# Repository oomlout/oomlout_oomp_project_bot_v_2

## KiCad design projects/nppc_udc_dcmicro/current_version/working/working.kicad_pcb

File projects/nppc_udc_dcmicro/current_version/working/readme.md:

# udc
 
## summary 
* id: nppc_udc_dcmicro
* user: nppc
* name: udc
* board: dcmicro
* repo: https://github.com/nppc/uDC
* src_file_repo_kicad_pcb: DCMicro.kicad_pcb
* src_file_repo_kicad_pcb_link: https://github.com/nppc/uDC/tree/master/DCMicro.kicad_pcb

* src_file_repo_sch: DCMicro.sch
* src_file_repo_sch_link: https://github.com/nppc/uDC/tree/master/DCMicro.sch
* full details link: https://github.com/oomlout/oomlout_oomp_project_bot_v_2/tree/main/projects/nppc_udc_dcmicro/current_version/working

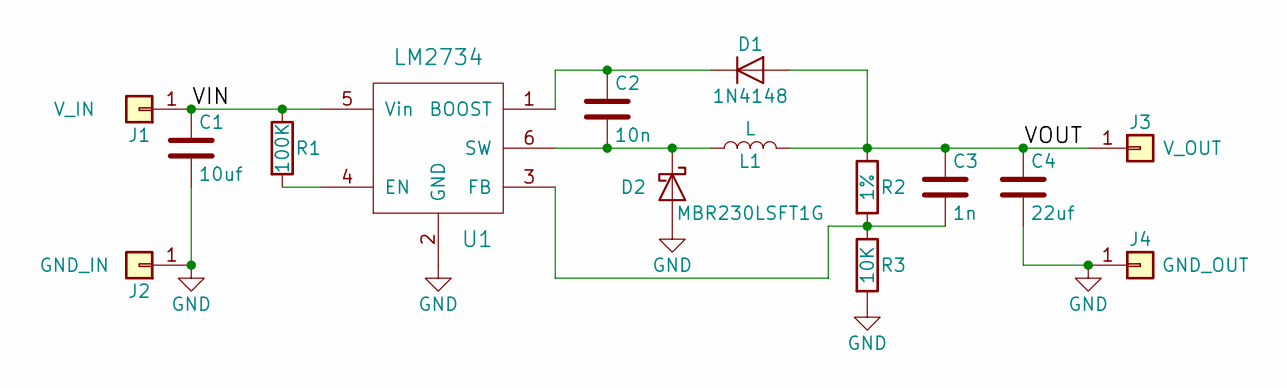
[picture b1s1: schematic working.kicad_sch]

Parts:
C1: 10uf; C_0603
C2: 10n; C_0402_NoSilk
C3: 1n; C_0402_NoSilk
C4: 22uf; C_0603
D1: 1N4148; D_SOD-523
D2: MBR230LSFT1G; D_SOD-123F
J1: V_IN; ESC_PWR_PAD
J2: GND_IN; ESC_PWR_PAD
J3: V_OUT; ESC_PWR_PAD
J4: GND_OUT; ESC_PWR_PAD
L1: L; Inductor-LPS4012
R1: 100K; R_0402_NoSilk
R2: 1%; R_0402_NoSilk
R3: 10K; R_0402_NoSilk
U1: LM2734; SOT-23-6

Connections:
/VIN: C1.1, J1.1, R1.1, U1.5 (Vin)
/VOUT: C3.1, C4.1, D1.2 (A), J3.1, L1.2, R2.1
GND: C1.2, C4.2, D2.2 (A), J2.1, J4.1, R3.2, U1.2 (GND)
unnamed: C2.1, D1.1 (K), U1.1 (BOOST)
unnamed: C2.2, D2.1 (K), L1.1, U1.6 (SW)
unnamed: C3.2, R2.2, R3.1, U1.3 (FB)
unnamed: R1.2, U1.4 (EN)

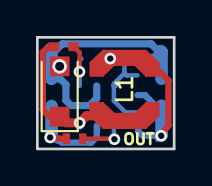
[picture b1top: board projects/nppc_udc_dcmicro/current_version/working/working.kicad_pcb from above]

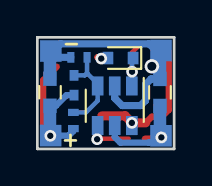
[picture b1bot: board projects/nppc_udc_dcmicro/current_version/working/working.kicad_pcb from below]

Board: 2 copper layers, 7.6 x 6.2 mm, 15 parts (11 on the bottom side), 7 nets.

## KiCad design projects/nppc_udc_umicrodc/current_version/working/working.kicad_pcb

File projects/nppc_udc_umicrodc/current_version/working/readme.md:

# udc
 
## summary 
* id: nppc_udc_umicrodc
* user: nppc
* name: udc
* board: umicrodc
* repo: https://github.com/nppc/uDC
* src_file_repo_kicad_pcb: uMicroDC/uMicroDC.kicad_pcb
* src_file_repo_kicad_pcb_link: https://github.com/nppc/uDC/tree/master/uMicroDC/uMicroDC.kicad_pcb

* src_file_repo_sch: uMicroDC/uMicroDC.sch
* src_file_repo_sch_link: https://github.com/nppc/uDC/tree/master/uMicroDC/uMicroDC.sch
* full details link: https://github.com/oomlout/oomlout_oomp_project_bot_v_2/tree/main/projects/nppc_udc_umicrodc/current_version/working

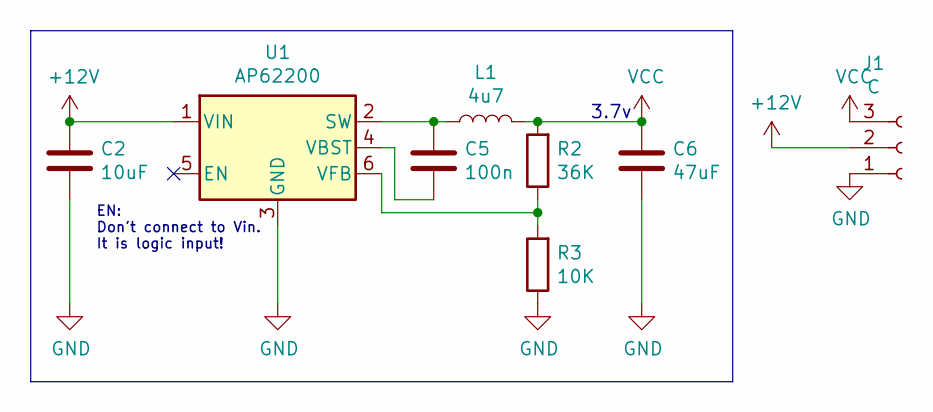
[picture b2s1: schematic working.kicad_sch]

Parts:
C2: 10uF; C_0805
C5: 100n; C_0603
C6: 47uF; C_0805
J1: C; Pin_Header_Angled_1x03_Pitch2.54mm
L1: 4u7; XFL2006-inductor
R2: 36K; R_0603
R3: 10K; R_0603
U1: AP62200; SOT-563

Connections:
+12V: C2.1, J1.2, U1.1 (VIN)
GND: C2.2, C6.2, J1.1, R3.1, U1.3 (GND)
unnamed: C5.1, L1.1, U1.2 (SW)
unnamed: C5.2, U1.4 (VBST)
unnamed: R2.1, R3.2, U1.6 (VFB)
VCC: C6.1, J1.3, L1.2, R2.2

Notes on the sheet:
3.7v
EN: Don't connect to Vin. It is logic input!

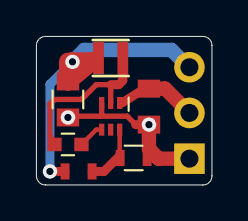
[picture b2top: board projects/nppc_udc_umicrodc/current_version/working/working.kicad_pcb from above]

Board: 2 copper layers, 9.8 x 8.2 mm, 8 parts (1 on the bottom side), 6 nets.

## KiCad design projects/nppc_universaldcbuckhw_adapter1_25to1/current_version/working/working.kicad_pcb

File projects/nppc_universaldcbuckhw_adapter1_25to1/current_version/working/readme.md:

# universaldcbuckhw
 
## summary 
* id: nppc_universaldcbuckhw_adapter1_25to1
* user: nppc
* name: universaldcbuckhw
* board: adapter1_25to1
* repo: https://github.com/nppc/UniversalDCBuckHW
* src_file_repo_kicad_pcb: KiCad/Adapter1-25to1/Adapter1-25to1.kicad_pcb
* src_file_repo_kicad_pcb_link: https://github.com/nppc/UniversalDCBuckHW/tree/master/KiCad/Adapter1-25to1/Adapter1-25to1.kicad_pcb

* src_file_repo_sch: KiCad/Adapter1-25to1/Adapter1-25to1.sch
* src_file_repo_sch_link: https://github.com/nppc/UniversalDCBuckHW/tree/master/KiCad/Adapter1-25to1/Adapter1-25to1.sch
* full details link: https://github.com/oomlout/oomlout_oomp_project_bot_v_2/tree/main/projects/nppc_universaldcbuckhw_adapter1_25to1/current_version/working

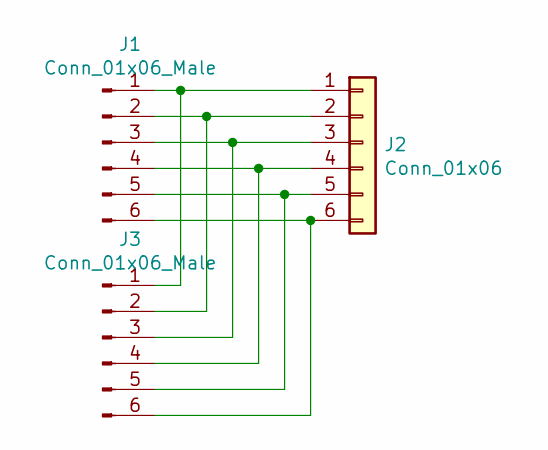
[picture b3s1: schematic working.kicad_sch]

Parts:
J1: Conn_01x06_Male; Pads_prog_6pin1.25mm
J2: Conn_01x06; JST_SH_6x1mm
J3: Conn_01x06_Male; Pin_Header_Angled_1x06_Pitch1.27mm

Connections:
unnamed: J1.1, J2.1, J3.1
unnamed: J1.2, J2.2, J3.2
unnamed: J1.3, J2.3, J3.3
unnamed: J1.4, J2.4, J3.4
unnamed: J1.5, J2.5, J3.5
unnamed: J1.6, J2.6, J3.6

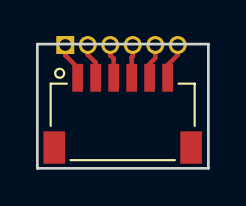
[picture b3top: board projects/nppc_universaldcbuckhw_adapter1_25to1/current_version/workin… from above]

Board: 2 copper layers, 9.5 x 6.9 mm, 3 parts (1 on the bottom side), 6 nets.

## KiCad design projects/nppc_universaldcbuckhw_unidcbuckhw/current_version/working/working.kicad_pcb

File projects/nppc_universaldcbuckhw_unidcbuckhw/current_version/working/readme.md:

# universaldcbuckhw
 
## summary 
* id: nppc_universaldcbuckhw_unidcbuckhw
* user: nppc
* name: universaldcbuckhw
* board: unidcbuckhw
* repo: https://github.com/nppc/UniversalDCBuckHW
* src_file_repo_kicad_pcb: KiCad/UniDCBuckHW.kicad_pcb
* src_file_repo_kicad_pcb_link: https://github.com/nppc/UniversalDCBuckHW/tree/master/KiCad/UniDCBuckHW.kicad_pcb

* src_file_repo_sch: KiCad/UniDCBuckHW.sch
* src_file_repo_sch_link: https://github.com/nppc/UniversalDCBuckHW/tree/master/KiCad/UniDCBuckHW.sch
* full details link: https://github.com/oomlout/oomlout_oomp_project_bot_v_2/tree/main/projects/nppc_universaldcbuckhw_unidcbuckhw/current_version/working

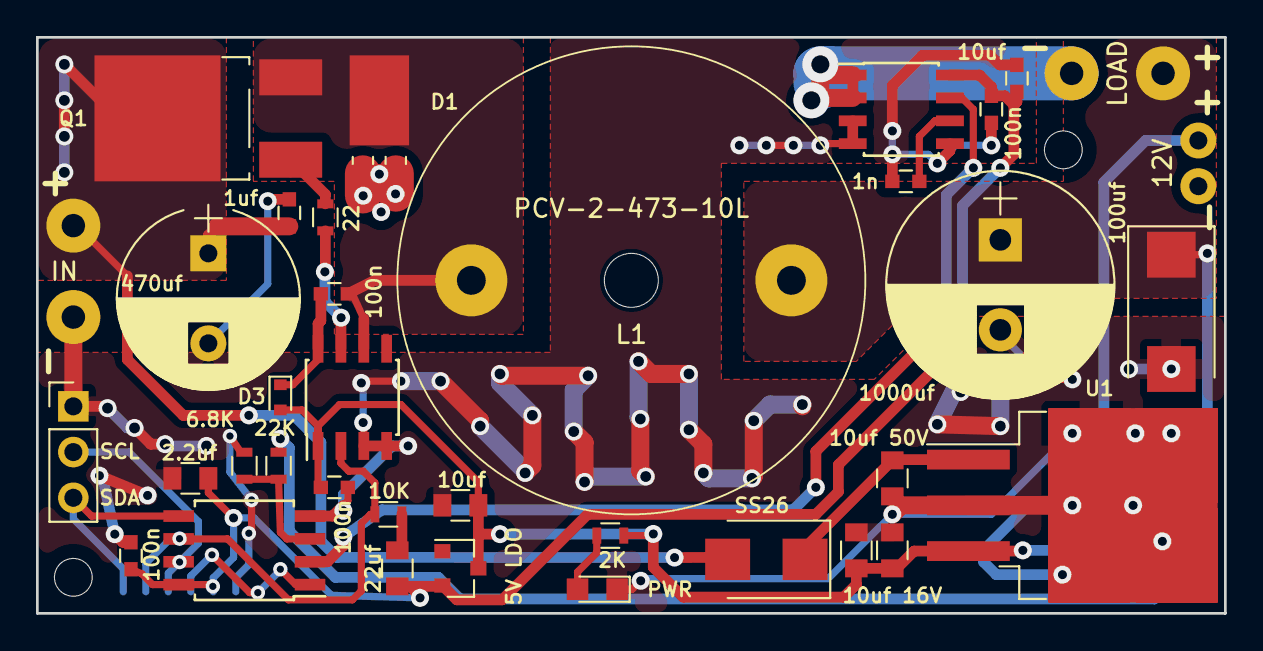
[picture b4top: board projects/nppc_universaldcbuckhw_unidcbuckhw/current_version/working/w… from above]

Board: 2 copper layers, 66.0 x 32.0 mm, 37 parts (1 on the bottom side), 19 nets.

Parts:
C1: 10uf 50V; C_0805
C2: 10uf; C_0805
C3, C5: 10uf 16V; C_0805
C4: 2.2uf; C_0805
C6: 470uf; CP_Radial_D10.0mm_P5.00mm
C7, C8, C11, C14: 100n; C_0603
C9: 1uf; C_0603
C10: 1000uf; CP_Radial_D12.5mm_P5.00mm
C12: 100uf; CP_Tantalum_Case-V_EIA-7343-20_Reflow
C13: 22uf; C_0805
C15: 1n; C_0603
C16: 10uf; C_0603
D1: PPS1045; D_Powermite3
D2: SS26; D_SMB
D3: 1N5819; D_SOD-523
D4: LED; LED_0805
J1: IN; Conn_Power
J2: 12V; Conn2pin_2.54mm
J3: i2c; Pin_Header_Straight_1x03_Pitch2.54mm
J4: LOAD; Conn_Power
J5: PROG; Pads_prog_6pin1.25mm
L1: 47uH; PCV-2-473-10L
Q1: IRLR8726PBF; TO-252-2_Rectifier
R1: 22K; R_0603
R2: 6.8K; R_0603
R3: 10K; R_0603
R4: 22; R_0603
R5: 2K; R_0603
U1: LM2940-12V; TO-263-3_TabPin2
U2: MCP1703-5V; SOT-23
U3: IR2101; SOIC-8_3.9x4.9mm_Pitch1.27mm
U4: ATTINY85-20SU; SOIJ-8_5.3x5.3mm_Pitch1.27mm
U5: ACS712-5; SOIC-8_3.9x4.9mm_Pitch1.27mm

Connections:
+5V: C4.2, C11.2, C13.2, C14.2, C16.2, J5.5, U2.2, U4.8, U5.8
+12V: C2.2, C3.2, C5.2, C7.2, D3.2, J2.2, R5.2, U1.3, U2.3, U3.1
/Isense: U4.2, U5.7
/PWM: J5.2, R3.2, U3.2, U4.6
/RST: J5.4, U4.1
/SCL: J3.2, J5.3, U4.7
/SDA: J3.3, J5.1, U4.5
/VOUT: C10.1, C12.1, J4.1, L1.2, R1.2
/Vsense: R1.1, R2.2, U4.3
GND: C1.1, C2.1, C3.1, C4.1, C5.1, C6.2, C7.1, C9.1, C10.2, C11.1, C12.2, C13.1, C14.1, C15.1, C16.1, D1.2, D4.1, J1.1, J2.1, J3.1, J5.6, R2.1, R3.1, U1.2, U2.1, U3.3, U3.4, U4.4, U5.3, U5.4, U5.5
unnamed: C1.2, D2.1, U1.1
unnamed: C6.1, C9.2, D2.2, J1.2, Q1.2
unnamed: C8.1, D1.1, L1.1, Q1.3, U3.6
unnamed: C8.2, D3.1, U3.8
unnamed: C15.2, U5.6
unnamed: D4.2, R5.1
unnamed: J4.2, U5.1, U5.2
unnamed: Q1.1, R4.1
unnamed: R4.2, U3.7

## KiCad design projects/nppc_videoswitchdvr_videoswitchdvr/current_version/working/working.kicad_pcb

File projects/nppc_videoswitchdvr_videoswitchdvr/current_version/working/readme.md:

# videoswitchdvr
 
## summary 
* id: nppc_videoswitchdvr_videoswitchdvr
* user: nppc
* name: videoswitchdvr
* board: videoswitchdvr
* repo: https://github.com/nppc/VideoSwitchDVR
* src_file_repo_kicad_pcb: KiCad/VideoSwitchDVR.kicad_pcb
* src_file_repo_kicad_pcb_link: https://github.com/nppc/VideoSwitchDVR/tree/master/KiCad/VideoSwitchDVR.kicad_pcb

* src_file_repo_sch: KiCad/VideoSwitchDVR.sch
* src_file_repo_sch_link: https://github.com/nppc/VideoSwitchDVR/tree/master/KiCad/VideoSwitchDVR.sch
* full details link: https://github.com/oomlout/oomlout_oomp_project_bot_v_2/tree/main/projects/nppc_videoswitchdvr_videoswitchdvr/current_version/working

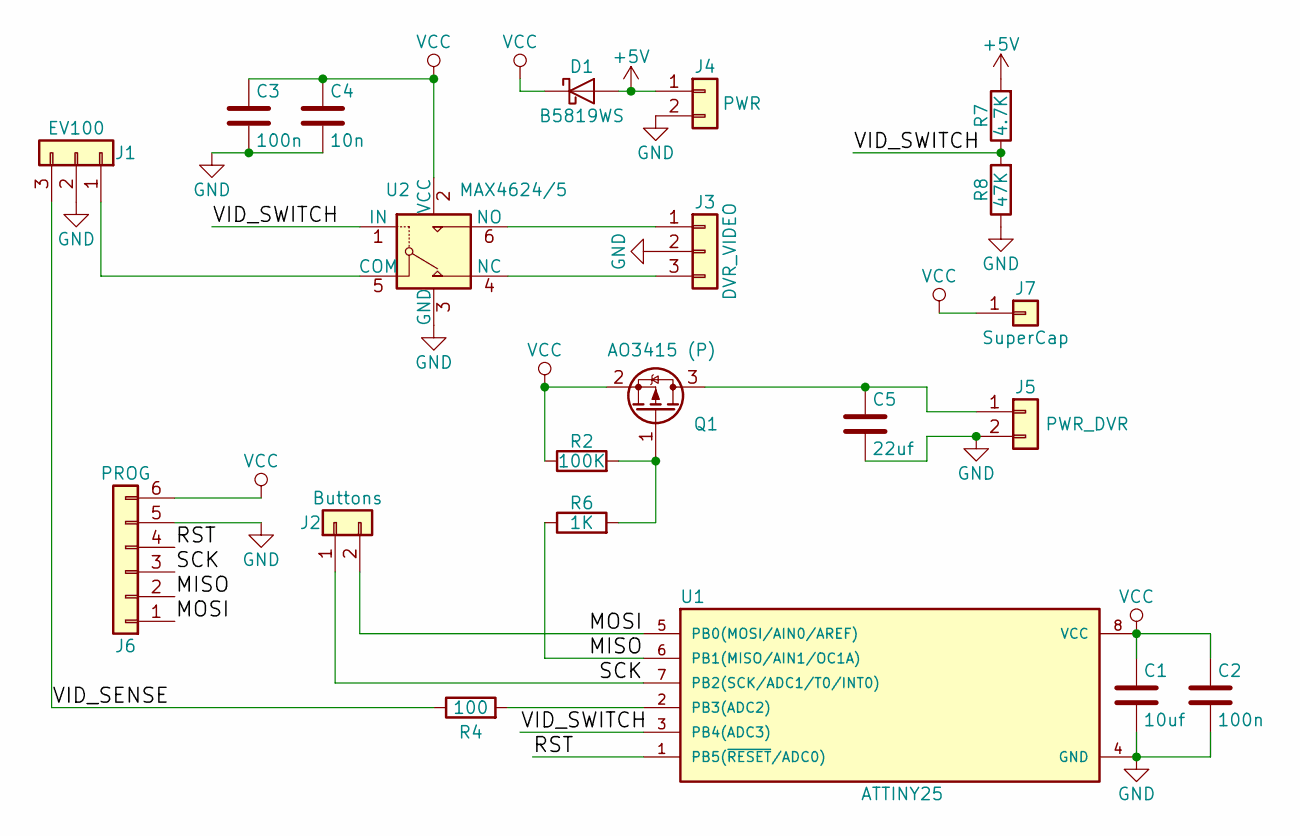
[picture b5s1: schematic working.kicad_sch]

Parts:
C1: 10uf; C_0603
C2, C3: 100n; C_0603
C4: 10n; C_0603
C5: 22uf; C_0805
D1: B5819WS; D_SOD-323
J1: EV100; USB_3_PADS
J2: Buttons; POWER2PIN
J3: DVR_VIDEO; USB_3_PADS
J4: PWR; POWER2PIN
J5: PWR_DVR; POWER2PIN
J6: PROG; Pads_prog_6pin1.25mm
J7: SuperCap; ESC_PWR_PAD
Q1: AO3415 (P); SOT-23
R2: 100K; R_0603
R4: 100; R_0603
R6: 1K; R_0603
R7: 4.7K; R_0603
R8: 47K; R_0603
U1: ATTINY25; SOIJ-8_5.3x5.3mm_Pitch1.27mm
U2: MAX4624/5; SOT-23-6

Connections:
+5V: D1.2 (A), J4.1, R7.2
/MISO: J6.2, R6.1, U1.6 (PB1(MISO/AIN1/OC1A))
/MOSI: J2.2, J6.1, U1.5 (PB0(MOSI/AIN0/AREF))
/RST: J6.4, U1.1 (PB5(~RESET/ADC0))
/SCK: J2.1, J6.3, U1.7 (PB2(SCK/ADC1/T0/INT0))
/VID_SENSE: J1.3, R4.1
/VID_SWITCH: R7.1, R8.2, U1.3 (PB4(ADC3)), U2.1 (IN)
GND: C1.2, C2.2, C3.2, C4.2, C5.2, J1.2, J3.2, J4.2, J5.2, J6.5, R8.1, U1.4 (GND), U2.3 (GND)
unnamed: C5.1, J5.1, Q1.3 (D)
unnamed: J1.1, U2.5 (COM)
unnamed: J3.1, U2.6 (NO)
unnamed: J3.3, U2.4 (NC)
unnamed: Q1.1 (G), R2.2, R6.2
unnamed: R4.2, U1.2 (PB3(ADC2))
VCC: C1.1, C2.1, C3.1, C4.1, D1.1 (K), J6.6, J7.1, Q1.2 (S), R2.1, U1.8 (VCC), U2.2 (VCC)

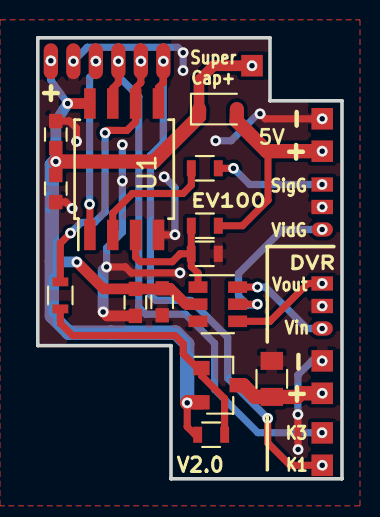
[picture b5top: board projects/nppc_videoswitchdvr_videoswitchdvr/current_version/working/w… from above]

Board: 2 copper layers, 16.9 x 24.5 mm, 21 parts (0 on the bottom side), 15 nets.

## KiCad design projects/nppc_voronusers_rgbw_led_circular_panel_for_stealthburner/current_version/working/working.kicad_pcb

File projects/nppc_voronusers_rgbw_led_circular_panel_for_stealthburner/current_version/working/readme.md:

# voronusers
 
## summary 
* id: nppc_voronusers_rgbw_led_circular_panel_for_stealthburner
* user: nppc
* name: voronusers
* board: rgbw_led_circular_panel_for_stealthburner
* repo: https://github.com/nppc/VoronUsers
* src_file_repo_kicad_pcb: printer_mods/VinnyCordeiro/RGB_LED_grid_for_SB/KiCad/RGBW_LED_circular_panel_for_Stealthburner.kicad_pcb
* src_file_repo_kicad_pcb_link: https://github.com/nppc/VoronUsers/tree/master/printer_mods/VinnyCordeiro/RGB_LED_grid_for_SB/KiCad/RGBW_LED_circular_panel_for_Stealthburner.kicad_pcb
* src_file_repo_kicad_sch: printer_mods/VinnyCordeiro/RGB_LED_grid_for_SB/KiCad/RGBW_LED_circular_panel_for_Stealthburner.kicad_sch
* src_file_repo_kicad_sch_link: https://github.com/nppc/VoronUsers/tree/master/printer_mods/VinnyCordeiro/RGB_LED_grid_for_SB/KiCad/RGBW_LED_circular_panel_for_Stealthburner.kicad_sch

* src_file_repo_sch: 
* src_file_repo_sch_link: https://github.com/nppc/VoronUsers/tree/master/
* full details link: https://github.com/oomlout/oomlout_oomp_project_bot_v_2/tree/main/projects/nppc_voronusers_rgbw_led_circular_panel_for_stealthburner/current_version/working

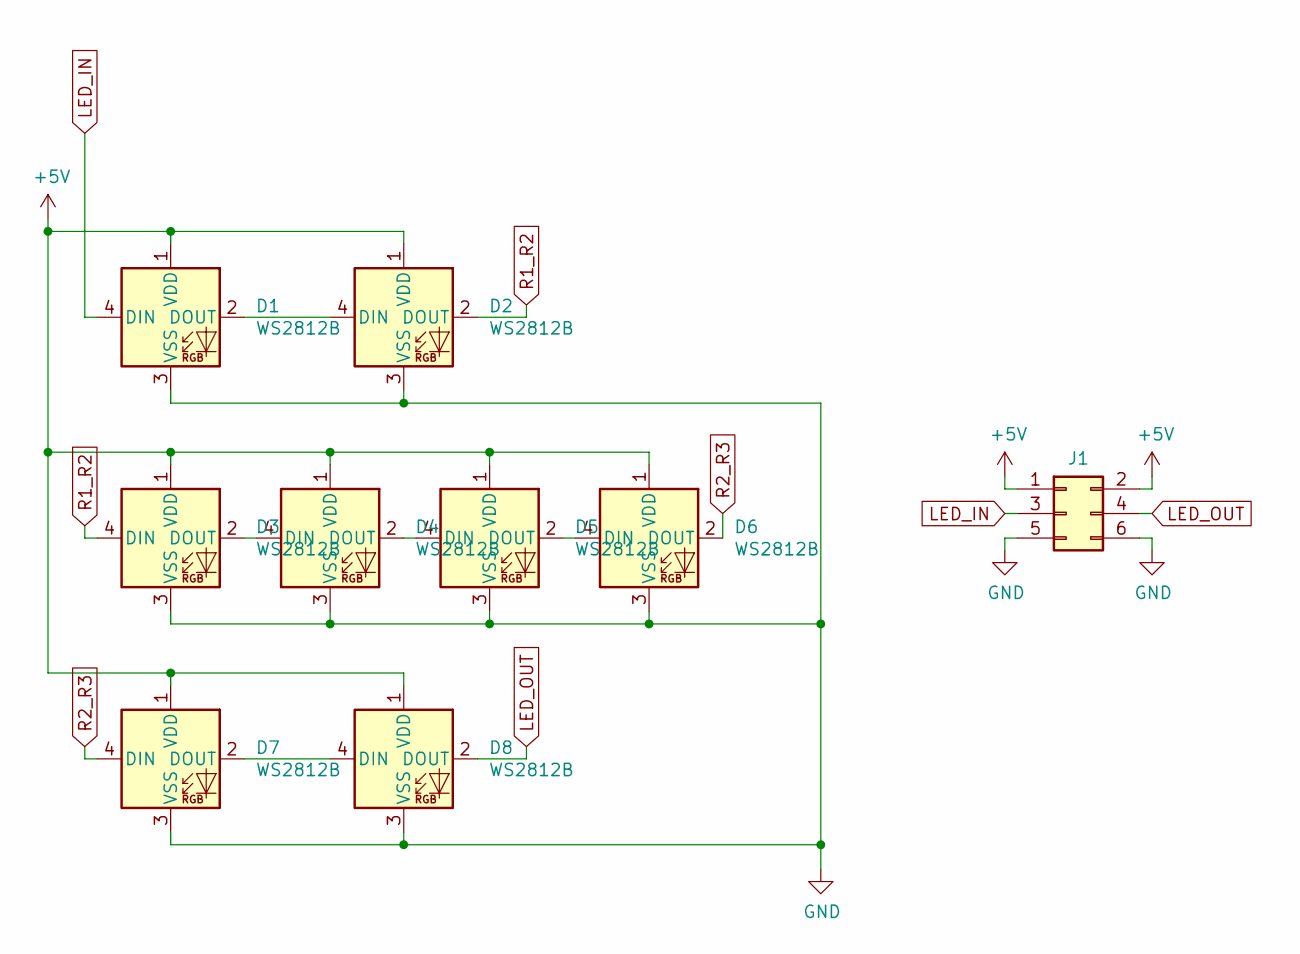
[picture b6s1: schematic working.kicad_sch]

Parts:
D1, D2, D3, D4, D5, D6, D7, D8: WS2812B; WS2812B-2020
J1: Conn_02x03_Odd_Even; Pin_Header_Straight_2x03_Pitch2.00mm_SMD

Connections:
+5V: D1.1 (VDD), D2.1 (VDD), D3.1 (VDD), D4.1 (VDD), D5.1 (VDD), D6.1 (VDD), D7.1 (VDD), D8.1 (VDD), J1.1, J1.2
GND: D1.3 (VSS), D2.3 (VSS), D3.3 (VSS), D4.3 (VSS), D5.3 (VSS), D6.3 (VSS), D7.3 (VSS), D8.3 (VSS), J1.5, J1.6
LED_IN: D1.4 (DIN), J1.3
LED_OUT: D8.2 (DOUT), J1.4
unnamed: D1.2 (DOUT), D2.4 (DIN)
unnamed: D3.2 (DOUT), D4.4 (DIN)
unnamed: D4.2 (DOUT), D5.4 (DIN)
unnamed: D5.2 (DOUT), D6.4 (DIN)
unnamed: D7.2 (DOUT), D8.4 (DIN)
R1_R2: D2.2 (DOUT), D3.4 (DIN)
R2_R3: D6.2 (DOUT), D7.4 (DIN)

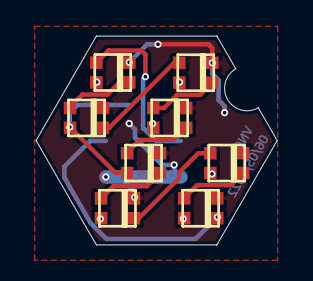
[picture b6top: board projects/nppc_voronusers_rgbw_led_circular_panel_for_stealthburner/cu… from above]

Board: 2 copper layers, 13.4 x 11.6 mm, 9 parts (1 on the bottom side), 11 nets.

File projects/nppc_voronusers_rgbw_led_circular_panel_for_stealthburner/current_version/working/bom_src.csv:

Comment,Designator,Footprint,LCSC
WS2812B,"D1,D2,D3,D4,D5,D6,D7,D8",WS2812B-2020,C965555
Conn_02x03_Odd_Even,J1,Pin_Header_Straight_2x03_Pitch2.00mm_SMD,

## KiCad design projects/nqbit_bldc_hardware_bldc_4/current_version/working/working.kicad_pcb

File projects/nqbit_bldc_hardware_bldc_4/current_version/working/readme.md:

# bldc_hardware
 
## summary 
* id: nqbit_bldc_hardware_bldc_4
* user: nqbit
* name: bldc_hardware
* board: bldc_4
* repo: https://github.com/nqbit/bldc-hardware
* src_file_repo_kicad_pcb: design/BLDC_4.kicad_pcb
* src_file_repo_kicad_pcb_link: https://github.com/nqbit/bldc-hardware/tree/master/design/BLDC_4.kicad_pcb

* src_file_repo_sch: design/BLDC_4.sch
* src_file_repo_sch_link: https://github.com/nqbit/bldc-hardware/tree/master/design/BLDC_4.sch
* full details link: https://github.com/oomlout/oomlout_oomp_project_bot_v_2/tree/main/projects/nqbit_bldc_hardware_bldc_4/current_version/working

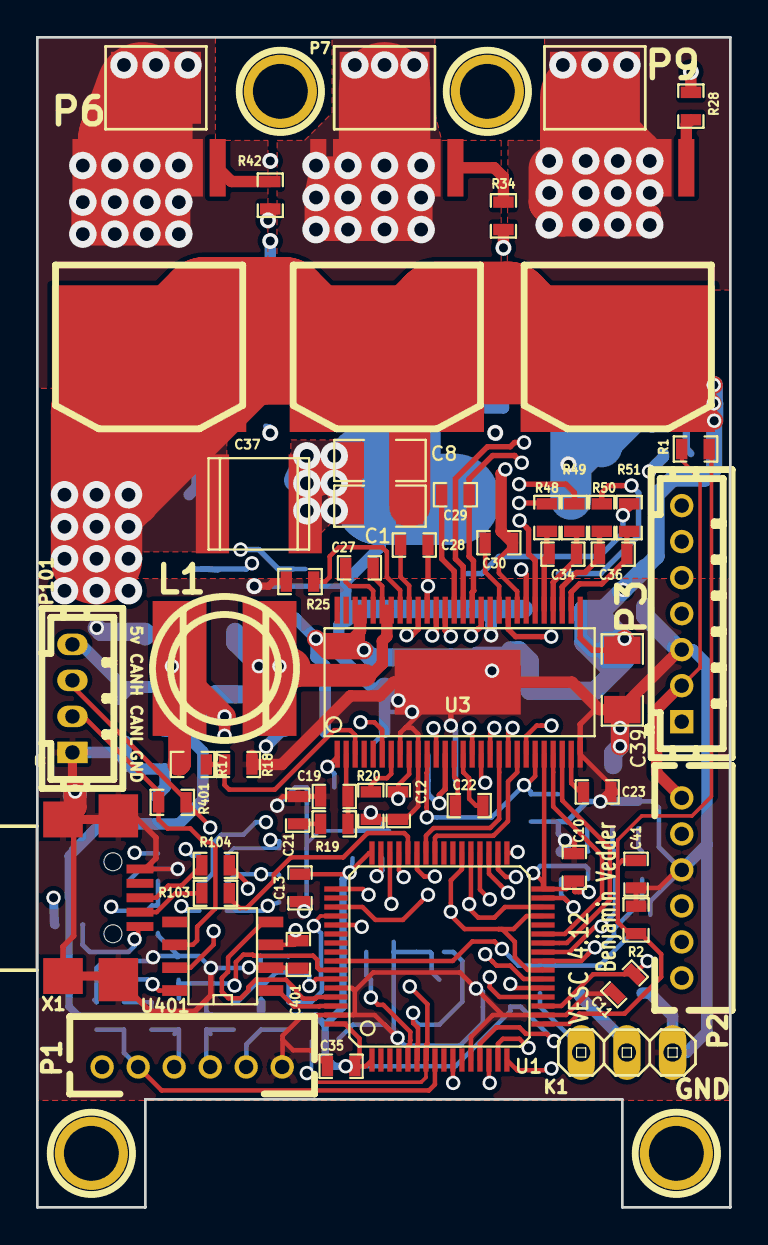
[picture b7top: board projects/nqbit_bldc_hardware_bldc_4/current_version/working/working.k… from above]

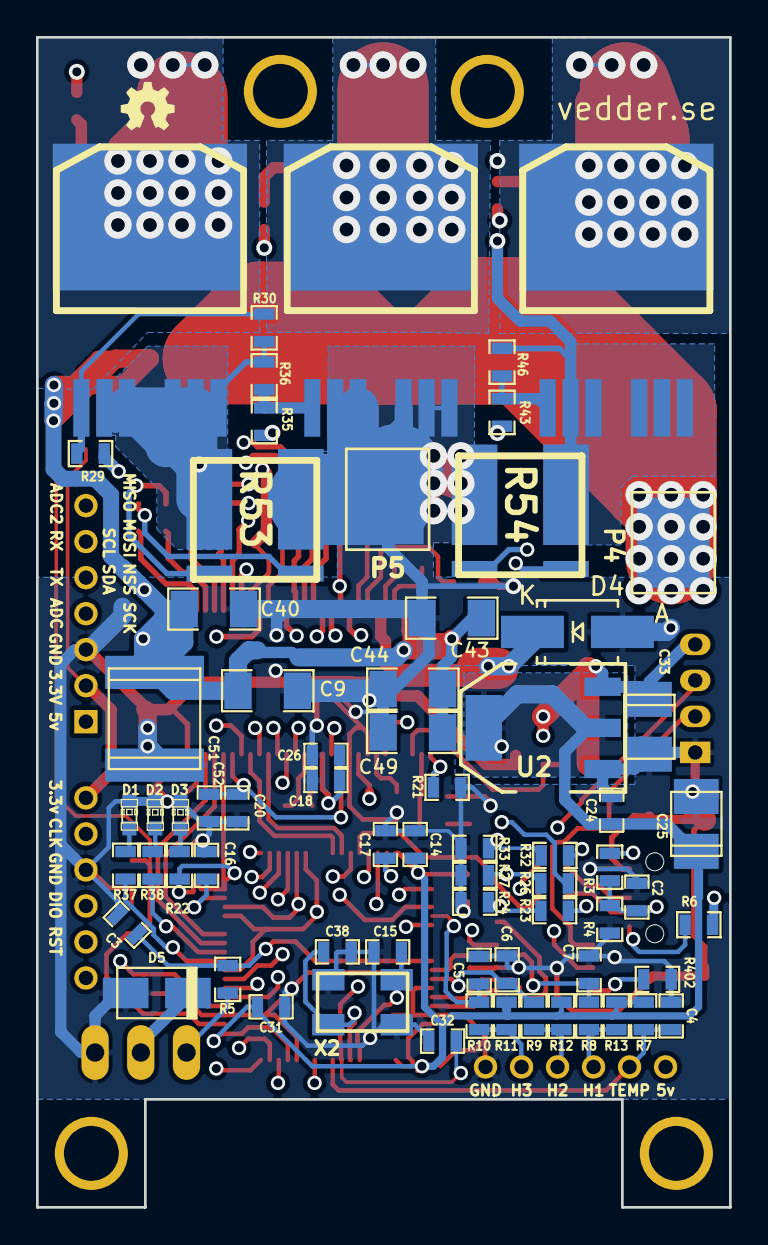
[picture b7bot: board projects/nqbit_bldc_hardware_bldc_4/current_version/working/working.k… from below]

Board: 4 copper layers, 38.5 x 65.0 mm, 126 parts (68 on the bottom side), 96 nets.

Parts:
1PIN, 1PIN#2, 1PIN#3, 1PIN#4: P***; 1pin
C1, C8, C9, C39, C40, C43, C44, C49: 10u,50V; SMD-1206
C2, C3, C27, C32: 100n; SMD-0603_c
C4, C5, C6, C7: 4n7; SMD-0603_c
C10, C11, C12, C13, C14, C16, C17, C18, C20, C23, C24, C26, C31, C35, C41, C52, C401: 2.2u; SMD-0603_c
C15, C38: 15p; SMD-0603_c
C19: 120p; SMD-0603_c
C21: 6.8n; SMD-0603_c
C22: 22n; SMD-0603_c
C25, C33: 100u; c_tant_B
C28, C29, C30: 220n; SMD-0603_c
C34, C36: 2.2n; SMD-0603_c
C37: 15u,100V; c_2220
C51: 15u, 100v; c_2220
D1: GREEN; LED-0603
D2: RED; LED-0603
D3: LED; LED-0603
D4: DIODESCH; SMA_Handsoldering
D5: TVS 5V; do214ac
K1: SERVO; pinhead-1X03
L1: 22u; inductor_smd_8x5mm
P1: HALL/Encoder; MICRO_JST_6
P2: SWD; MICRO_JST_6
P3: PWR_COMM; b7b-ph-kl
P4: IN+; 1PAD_4x5mm
P5: IN-; 1PAD_4x5mm
P6: MOTOR1; 1PAD_4x5mm
P7: MOTOR2; 1PAD_4x5mm
P9: MOTOR3; 1PAD_4x5mm
P101: CANBUS; b4b-ph-kl
Q1, Q2, Q3, Q4, Q5, Q6: IRFS7530; D2PAK-7-GDS
R1: NTC 10k; SMD-0603_r
R2, R7, R8, R9, R10, R20, R402: 10k; SMD-0603_r
R3, R23, R26, R30, R32, R36, R46: 39k; SMD-0603_r
R4, R5, R11, R12, R13, R22, R24, R27, R33: 2k2; SMD-0603_r
R6: 0R; SMD-0603_r
R17: 18k; SMD-0603_r
R18: 3k3; SMD-0603_r
R19: 15k; SMD-0603_r
R21: 220k; SMD-0603_r
R25: 1M; SMD-0603_r
R28, R29, R34, R35, R42, R43: 4R7; SMD-0603_r
R37, R38, R48, R49, R50, R51: 100R; SMD-0603_r
R53, R54: SHUNT; WSLP2726
R103, R104: 22R; SMD-0603_r
R401: NI; SMD-0603_r
U1: STM32F40X_LQFP64; lqfp64_pad_mod
U2: TC2117; SOT-223
U3: DRV8302; TSSOP-56-PP
U401: SN65HVD232; SOIC-8-W
X1: MINI-USB-SHIELD-32005-201; USB-UX60R-MB-5ST
X2: 8MHz 10ppm; Crystal_5x3mm

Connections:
+5V: C33.1, D5.2, K1.2, L1.2, P1.1, P3.1, P101.4, R6.2, R17.1, U2.3
/CAN bus transceiver/CANH: P101.3, R401.1, U401.7
/CAN bus transceiver/CANL: P101.2, R401.2, U401.6
/CAN bus transceiver/CAN_RX: U1.61, U401.4
/CAN bus transceiver/CAN_TX: U1.62, U401.1
/Filters/HALL1_IN: P1.3, R8.1, R13.1
/Filters/HALL1_OUT: C7.1, R8.2, U1.58
/Filters/HALL2_IN: P1.4, R9.1, R12.1
/Filters/HALL2_OUT: C6.1, R9.2, U1.59
/Filters/HALL3_IN: P1.5, R10.1, R11.1
/Filters/HALL3_OUT: C5.1, R10.2, U1.52
/Filters/TEMP_IN: C4.2, P1.2, R7.1, U1.8
/MCU/ADC_TEMP: C41.1, R1.2, R2.1, U1.17
/MCU/AN_IN: C2.2, R3.2, R4.2, U1.10
/MCU/BR_SO1: U1.27, U3.25
/MCU/BR_SO2: U1.26, U3.26
/MCU/DC_CAL: U1.33, U3.12
/MCU/EN_GATE: U1.51, U3.16
/MCU/FAULT: U1.53, U3.6
/MCU/H1: U1.43, U3.17
/MCU/H2: U1.42, U3.19
/MCU/H3: U1.41, U3.21
/MCU/L1: U1.36, U3.18
/MCU/L2: U1.35, U3.20
/MCU/L3: U1.34, U3.22
/MCU/LED_GREEN: R37.2, U1.24
/MCU/LED_RED: R38.2, U1.25
/MCU/MISO_ADC_EXT2: P3.7, U1.22
/MCU/RX_SCL_MOSI: P3.6, U1.23, U1.29, U1.38
/MCU/SCK_ADC_EXT: P3.4, U1.21
/MCU/SENS1: R23.2, R24.2, U1.16
/MCU/SENS2: R26.2, R27.2, U1.15
/MCU/SENS3: R32.2, R33.2, U1.14
/MCU/SERVO: C3.2, R5.1, U1.57
/MCU/TX_SDA_NSS: P3.5, U1.20, U1.30, U1.37
/MCU/USB_DM: R103.1, U1.44
/MCU/USB_DP: R104.1, U1.45
/Mosfet driver/H1_LOW: Q2.S, R30.1, R36.1, R53.2, U3.44
/Mosfet driver/H1_VS: C28.1, P9.1, Q1.S, Q2.D, R32.1, U3.46
/Mosfet driver/H2_VS: C29.1, P7.1, Q3.S, Q4.D, R26.1, U3.41
/Mosfet driver/H3_LOW: Q6.S, R46.1, R54.1, U3.34
/Mosfet driver/H3_VS: C30.1, P6.1, Q5.S, Q6.D, R23.1, U3.36
/Mosfet driver/M_H1: R28.2, U3.47
/Mosfet driver/M_H2: R34.2, U3.42
/Mosfet driver/M_H3: R42.2, U3.37
/Mosfet driver/M_L1: R29.2, U3.45
/Mosfet driver/M_L2: R35.2, U3.40
/Mosfet driver/M_L3: R43.2, U3.35
/Mosfet driver/SH1_A: R48.1, R54.3
/Mosfet driver/SH1_B: R49.1, R54.4
/Mosfet driver/SH2_A: R50.1, R53.4
/Mosfet driver/SH2_B: R51.1, R53.3
GND: C1.1, C2.1, C3.1, C4.1, C5.2, C6.2, C7.2, C8.1, C9.1, C10.1, C11.1, C12.1, C13.1, C14.1, C15.2, C16.2, C17.2, C18.2, C19.1, C20.1, C21.1, C23.1, C24.2, C25.2, C26.2, C31.1, C32.1, C33.2, C35.1, C37.1, C38.2, C39.1, C40.1, C41.2, C43.2, C44.2, C49.2, C51.1, C52.1, C401.2, D1.2, D2.2, D3.2, D4.1, D5.1, K1.3, P1.6, P2.3, P3.3, P5.1, P101.1, Q4.S, R2.2, R4.1, R18.2, R20.2, R21.1, R24.1, R25.1, R27.1, R33.1, R53.1, R54.2, R402.2, U1.12, U1.18, U1.60, U1.63, U2.1, U3.8, U3.10, U3.28, U3.39, U3.57, U401.2, X1.5, X2.3
NRST: C32.2, P2.5, U1.7
unnamed: C15.1, U1.5, X2.1
unnamed: C16.1, U1.31
unnamed: C17.1, U1.47
unnamed: C18.1, C26.1, U3.13
unnamed: C19.2, R19.2, U3.2
unnamed: C20.2, C52.2, U3.11, U3.23
unnamed: C21.2, R19.1
unnamed: C22.1, U3.14
unnamed: C22.2, U3.15
unnamed: C23.2, U3.27
unnamed: C27.1, D4.2, L1.1, U3.50, U3.51
unnamed: C27.2, U3.52
unnamed: C28.2, U3.48
unnamed: C29.2, U3.43
unnamed: C30.2, U3.38
unnamed: C34.1, R48.2, U3.33
unnamed: C34.2, R49.2, U3.32
unnamed: C36.1, R50.2, U3.31
unnamed: C36.2, R51.2, U3.30
unnamed: C38.1, U1.6, X2.2
unnamed: D1.1, R37.1
unnamed: D2.1, R38.1
unnamed: D3.1, R22.1
unnamed: K1.1, R5.2
unnamed: Q1.G, R28.1
unnamed: Q2.G, R29.1, R30.2
unnamed: Q3.G, R34.1
unnamed: Q4.G, R35.1, R36.2
unnamed: Q5.G, R42.1
unnamed: Q6.G, R43.1, R46.2
unnamed: R6.1, X1.1
unnamed: R17.2, R18.1, U3.3
unnamed: R20.1, U3.7
unnamed: R21.2, U3.1
unnamed: R25.2, U3.49
unnamed: R103.2, X1.2
unnamed: R104.2, X1.3
unnamed: R402.1, U401.8
SWCLK: P2.2, U1.49
SWDIO: P2.4, U1.46
VCC: C10.2, C11.2, C12.2, C13.2, C14.2, C24.1, C25.1, C31.2, C35.2, C401.1, P2.1, P3.2, R1.1, R7.2, R11.2, R12.2, R13.2, R22.2, U1.1, U1.13, U1.19, U1.32, U1.48, U1.64, U2.2, U3.9, U3.24, U401.3
V_SUPPLY: C1.2, C8.2, C9.2, C37.2, C39.2, C40.2, C43.1, C44.1, C49.1, C51.2, P4.1, Q1.D, Q3.D, Q5.D, R3.1, U3.29, U3.53, U3.54
